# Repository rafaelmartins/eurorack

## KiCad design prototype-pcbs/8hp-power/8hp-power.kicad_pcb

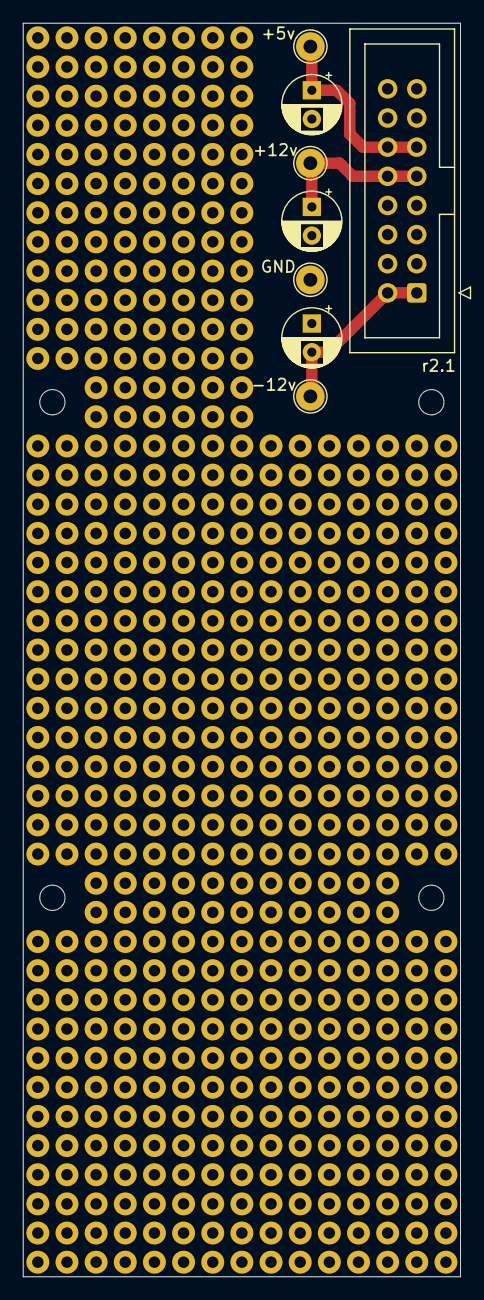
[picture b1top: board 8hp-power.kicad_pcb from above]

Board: 2 copper layers, 38.1 x 109.2 mm, 8 parts (0 on the bottom side), 4 nets.

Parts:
C1, C2, C3: CP; CP_Radial_D5.0mm_P2.50mm
J1: IDC Header 2x8; IDC-Header_2x08_P2.54mm_Vertical
TP1: +5v; TestPoint_THTPad_D2.5mm_Drill1.2mm
TP2: +12v; TestPoint_THTPad_D2.5mm_Drill1.2mm
TP3: GND; TestPoint_THTPad_D2.5mm_Drill1.2mm
TP4: -12v; TestPoint_THTPad_D2.5mm_Drill1.2mm

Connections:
+5V: C1.1, J1.11, J1.12, TP1.1
+12V: C2.1, J1.9, J1.10, TP2.1
-12V: C3.2, J1.1, J1.2, TP4.1
GND: C1.2, C2.2, C3.1, J1.3, J1.4, J1.5, J1.6, J1.7, J1.8, TP3.1
